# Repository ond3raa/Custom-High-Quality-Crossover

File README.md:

# Description
This is an audio crossover. Its function is to take an audio signal and split it into multiple speakers based on specific frequencies. It is used in speaker cabinets and sound systems to achieve the correct sound.

# How to use
The usage is quite simple: just assemble the PCB, solder the cables from the amplifier to the input, and connect the mid-bass speaker to the "woofer" output and the tweeter to the "tweeter" output.

# Why I made this
I created this project because I built speaker cabinets using car speakers and wired them the same way they were in the car. At frequencies around 2-10kHz, both speakers played simultaneously due to the missing 2nd-
order crossover, and the sound was sharp and aggressive. I designed this 2nd-order crossover to audibly eliminate this problem and improve the overall sound quality.

# Firmware & Software
This project is a passive analog audio crossover. It uses only discrete components, including capacitors, inductors, and resistors for frequency filtering. There are no microcontrollers or integrated circuits involved, so no firmware is required for this project to operate.

### BOM

| Part | Value | Quantity | Price (CZK) | Link |
| :--- | :--- | :--- | :--- | :--- |
| Connecting cables | | 6 | 0 - I have them | - |
| Mounting screws | M3 | 8 | 0 - I have them | - |
| Air coil L1 | 0.33mH | 2 | 260 | [Link](https://www.reproobchod.cz/dexon-vzduchova-civka-0-33mh-0-8mm/) |
| Air coil L2 | 0.47mH | 2 | 338 | [Link](https://www.reproobchod.cz/monacor-lsip-47-2-vzduchova-civka-0-47mh-0-85mm/) |
| Capacitor C1 | 8.2uF | 2 | 192 | [Link](https://www.reproobchod.cz/kondenzator-monacor-mkpa-82-8-2uf-250v-dc-mkp/) |
| Capacitor C2 | 6.8uF | 2 | 190 | [Link](https://www.reproobchod.cz/kondenzator-monacor-mkpa-68-6-8uf-250v-dc-mkp/) |
| Resistor R1 | 1 Ohm | 2 | 60 | [Link](https://www.reproobchod.cz/rezistor-keramicky-visaton-r-1ohm-10-w/) |
| Resistor R2 | 1.5 Ohm | 2 | 60 | [Link](https://www.reproobchod.cz/rezistor-keramicky-visaton-r-1-5ohm-10-w/) |
| Resistor R3 | 2.2 Ohm | 2 | 36 | [Link](https://www.reproobchod.cz/rezistor-keramicky-dratovy-tesla-tr271-2r2-10w/) |
| Resistor R4 | 3 Ohm | 2 | 36 | [Link](https://www.reproobchod.cz/rezistor-keramicky-dratovy-tesla-tr271-3r0-10w/) |
| Shipping | reproobchod.cz | 1 | 69 | - |
| PCB | JLCPCB | 2 | ~90 | [Link](https://jlcpcb.com/) |
| **Total to pay** | | | **1331 CZK** | **~$63.97 USD** |

## Note:
## The real value in dollars is here in the BOM. It is also in the blueprint project, but it differs due to different exchange rates
The 3D component models used in the CAD assembly and STEP file are **representative placeholders**.

I selected these models based on their physical dimensions (length and width) to verify component clearance and PCB seating. The actual high-quality audio components (inductors and capacitors) used for assembly are precisely specified in the **Bill of Materials**.

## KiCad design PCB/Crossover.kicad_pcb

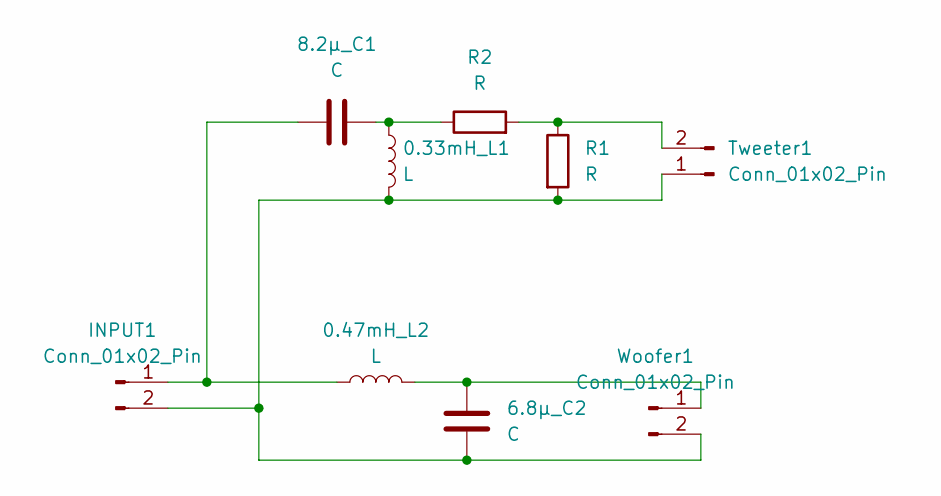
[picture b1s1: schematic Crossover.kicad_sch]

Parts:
0.33mH_L1: L; DEXON vzduchová cívka 0,8mm
0.47mH_L2: L; MONACOR LSIP-472
6.8µ_C2: C; MONACOR MKPA-68
8.2µ_C1: C; MONACOR MKPA-82
INPUT1: Conn_01x02_Pin; Konektor připojovací
R1, R2: R; Rezistor keramický
Tweeter1: Conn_01x02_Pin; Konektor připojovací
Woofer1: Conn_01x02_Pin; Konektor připojovací

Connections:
unnamed: 0.33mH_L1.1, 8.2µ_C1.2, R2.1
unnamed: 0.47mH_L2.1, 8.2µ_C1.1, INPUT1.1
unnamed: 0.33mH_L1.2, 6.8µ_C2.2, INPUT1.2, R1.2, Tweeter1.1, Woofer1.2
unnamed: R1.1, R2.2, Tweeter1.2
unnamed: 0.47mH_L2.2, 6.8µ_C2.1, Woofer1.1

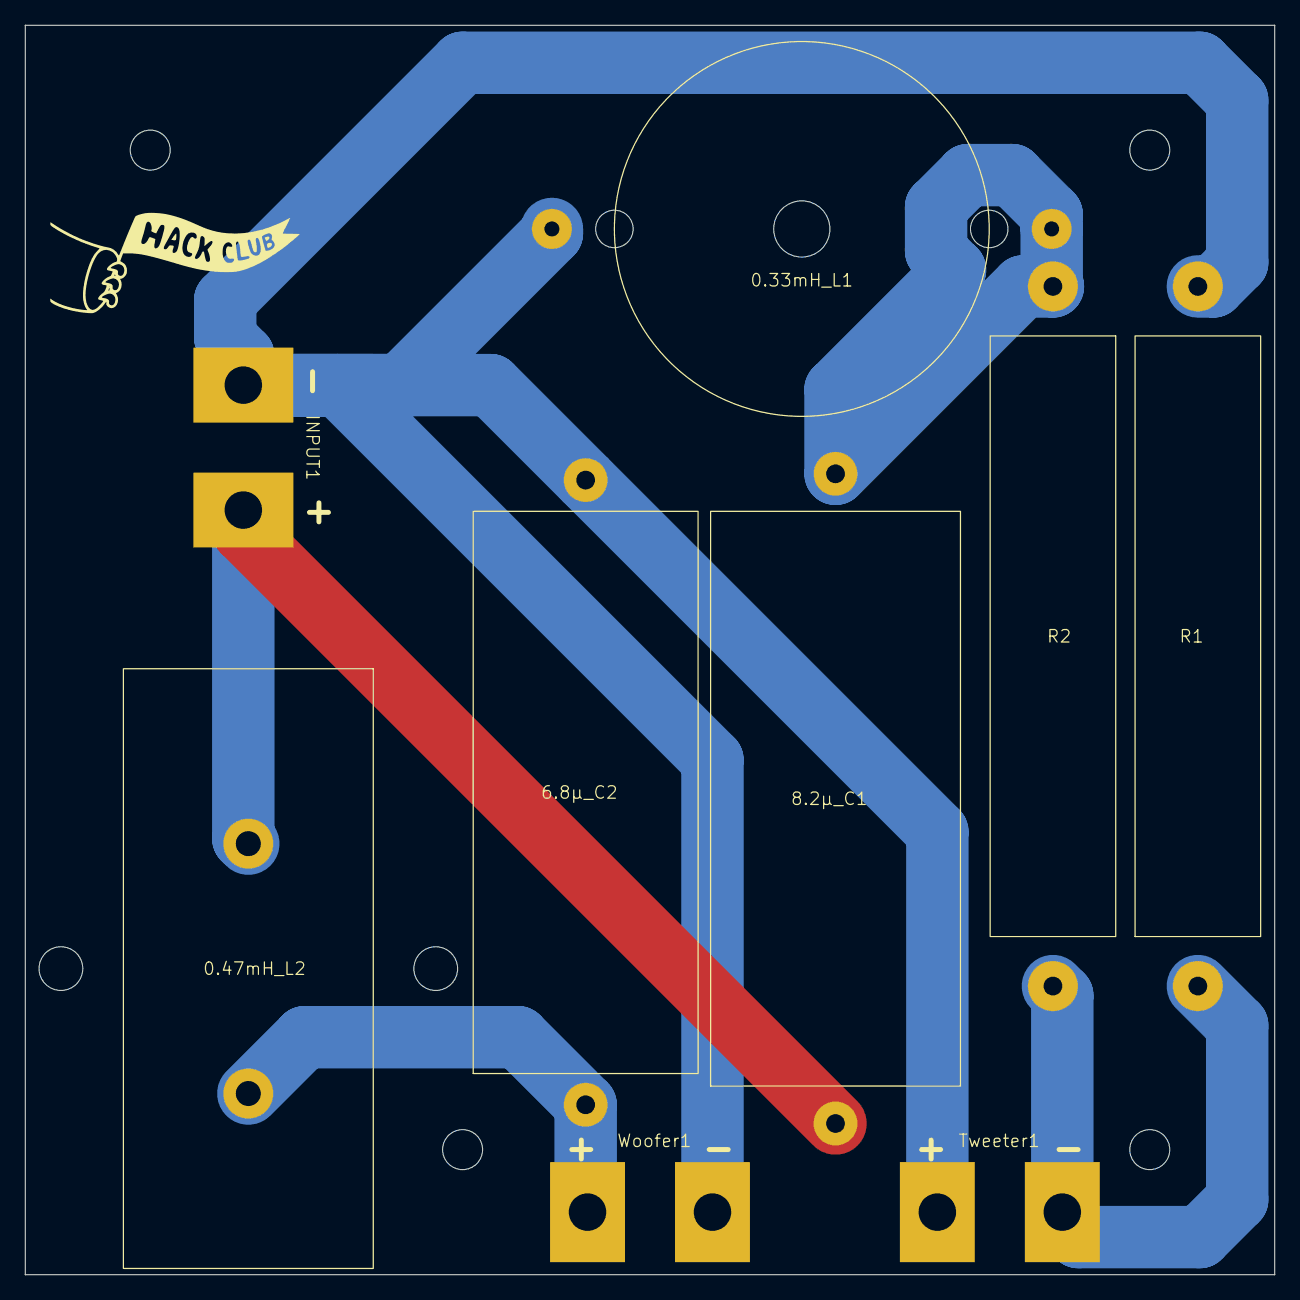
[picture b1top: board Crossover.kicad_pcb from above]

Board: 2 copper layers, 100.0 x 100.0 mm, 9 parts (0 on the bottom side), 5 nets.

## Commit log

2026-03-15 Created pcb folder
2026-03-15 Added kicad files
2026-03-15 Create PCB
2026-03-16 Add Assets
2026-03-17 Add BOM.csv
2026-03-17 Add gerbers zip
2026-03-17 Add step model
2026-03-17 Add used models
2026-04-11 Rename Assets/Bez názvu.jpg to Frequency Response.jpg
